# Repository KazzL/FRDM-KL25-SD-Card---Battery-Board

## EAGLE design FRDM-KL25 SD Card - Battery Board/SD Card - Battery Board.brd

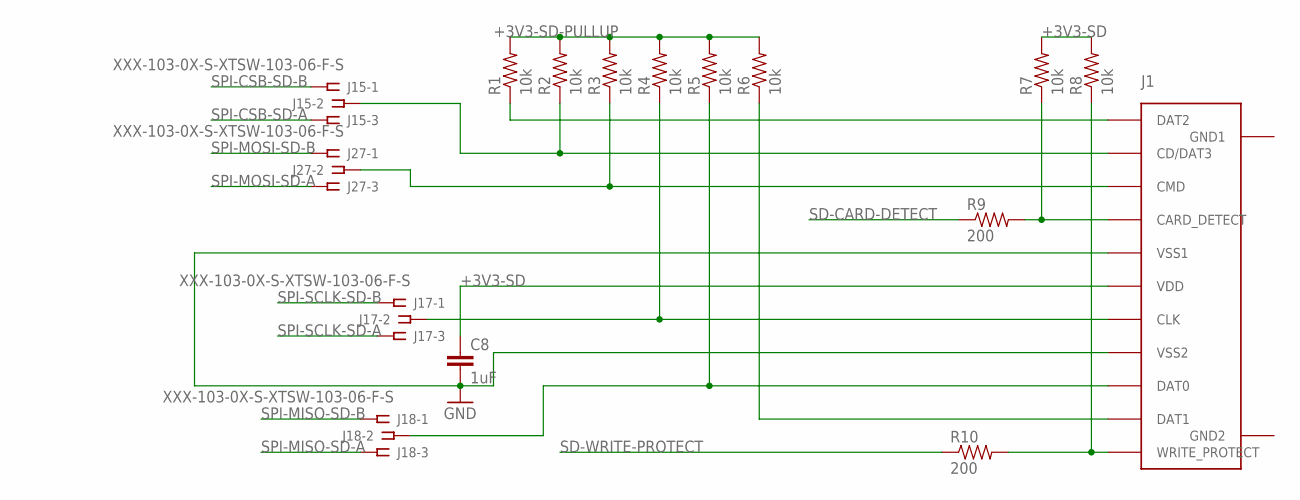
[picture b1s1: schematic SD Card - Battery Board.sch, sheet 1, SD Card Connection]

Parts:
C8: 1uF; C0402
J1: SD_CARD_SLOT; 693061010911
J15, J17, J18, J27: XXX-103-0X-S-XTSW-103-06-F-S; XXX-103-0X-S-X
R1, R2, R3, R4, R5, R6, R7, R8: 10k; R0603
R9, R10: 200; R0603

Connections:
+3V3-SD: C8.1, J1.P$4 (VDD), R7.2, R8.2; also elsewhere on the board
+3V3-SD-PULLUP: R1.2, R2.2, R3.2, R4.2, R5.2, R6.2; also elsewhere on the board
GND: C8.2, J1.P$3 (VSS1), J1.P$6 (VSS2); also elsewhere on the board
unnamed: J1.P$9 (DAT2), R1.1
unnamed: J1.P$10 (CARD_DETECT), R7.1, R9.2
unnamed: J1.P$1 (CD/DAT3), J15.2, R2.1
unnamed: J1.P$8 (DAT1), R6.1
unnamed: J1.P$11 (WRITE_PROTECT), R8.1, R10.2
unnamed: J1.P$2 (CMD), J27.2, R3.1
unnamed: J1.P$5 (CLK), J17.2, R4.1
unnamed: J1.P$7 (DAT0), J18.2, R5.1
SD-CARD-DETECT: R9.1; also elsewhere on the board
SD-WRITE-PROTECT: R10.1; also elsewhere on the board
SPI-CSB-SD-A: J15.3; also elsewhere on the board
SPI-CSB-SD-B: J15.1; also elsewhere on the board
SPI-MISO-SD-A: J18.3; also elsewhere on the board
SPI-MISO-SD-B: J18.1; also elsewhere on the board
SPI-MOSI-SD-A: J27.3; also elsewhere on the board
SPI-MOSI-SD-B: J27.1; also elsewhere on the board
SPI-SCLK-SD-A: J17.3; also elsewhere on the board
SPI-SCLK-SD-B: J17.1; also elsewhere on the board

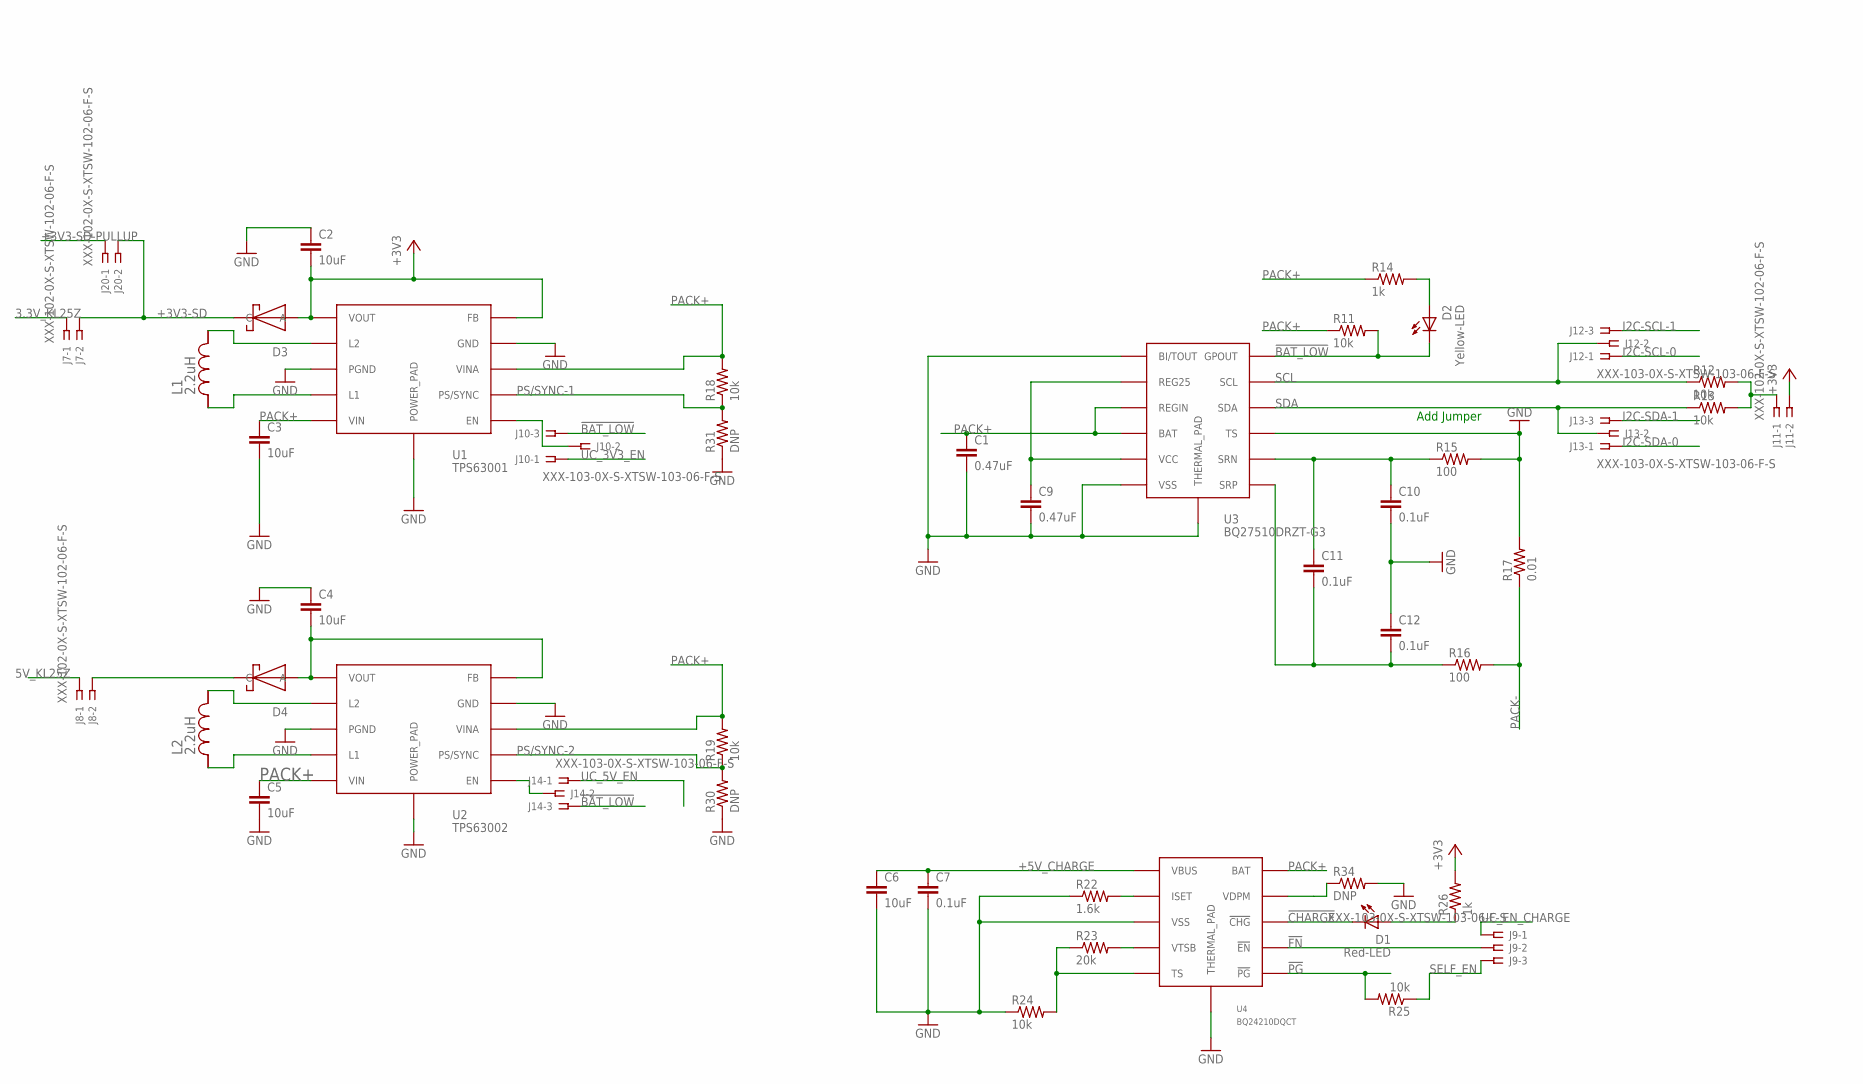
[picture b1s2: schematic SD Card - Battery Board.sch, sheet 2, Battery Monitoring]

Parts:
C1, C9: 0.47uF; C0402
C2, C3, C4, C5, C6: 10uF; C0402
C7, C10, C11, C12: 0.1uF; C0402
D1: Red-LED; 1.25X1.4
D2: Yellow-LED; 1.25X1.4
D3, D4: SCHOTTKY; SC-90
J7, J8, J11, J20: XXX-102-0X-S-XTSW-102-06-F-S; XXX-102-0X-S-X
J9, J10, J12, J13, J14: XXX-103-0X-S-XTSW-103-06-F-S; XXX-103-0X-S-X
L1, L2: 2.2uH; NRS401X
R11, R12, R13, R18, R19, R24, R25: 10k; R0402
R14, R26: 1k; R0402
R15, R16: 100; R0402
R17: 0.01; R0603
R22: 1.6k; R0402
R23: 20k; R0402
R30, R31, R34: DNP; R0402
U1: TPS63001; VFDFN-10
U2: TPS63002; VFDFN-10
U3: BQ27510DRZT-G3; VFDFN-12
U4: BQ24210DQCT; WFDFN-10

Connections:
3.3V_KL25Z: J7.1; also elsewhere on the board
5V_KL25Z: J8.1; also elsewhere on the board
!BAT_LOW: D2.P$2 (C), J10.3, J14.3, R11.2, U3.P$12 (GPOUT)
!CHARGE: D1.P$2 (C), U4.P$8 (!CHG)
!FN: J9.2, U4.P$7 (!EN)
!PG: R25.2, U4.P$6 (!PG)
+3V3: C2.2, D3.P$2 (A), J11.2, R26.2, U1.P$1 (VOUT), U1.P$10 (FB)
+3V3-SD: D3.P$1 (C), J7.2, J20.2; also elsewhere on the board
+3V3-SD-PULLUP: J20.1; also elsewhere on the board
+5V_CHARGE: C6.1, C7.1, U4.P$1 (VBUS); also elsewhere on the board
GND: C1.2, C2.1, C3.2, C4.1, C5.2, C6.2, C7.2, C9.2, C10.2, C12.1, R15.2, R17.2, R22.1, R24.1, R30.1, R31.1, R34.2, U1.P$3 (PGND), U1.P$9 (GND), U1.P$11 (POWER_PAD), U2.P$3 (PGND), U2.P$9 (GND), U2.P$11 (POWER_PAD), U3.P$1 (BI/TOUT), U3.P$6 (VSS), U3.P$9 (TS), U3.P$13 (THERMAL_PAD), U4.P$3 (VSS), U4.P$11 (THERMAL_PAD); also elsewhere on the board
I2C-SCL-0: J12.1; also elsewhere on the board
I2C-SCL-1: J12.3; also elsewhere on the board
I2C-SDA-0: J13.1; also elsewhere on the board
I2C-SDA-1: J13.3; also elsewhere on the board
unnamed: C9.1, U3.P$2 (REG25), U3.P$5 (VCC)
unnamed: J10.2, U1.P$6 (EN)
unnamed: R34.1, U4.P$9 (VDPM)
unnamed: J11.1, R12.2, R13.2
unnamed: D2.P$1 (A), R14.2
unnamed: C11.2, C12.2, R16.1, U3.P$7 (SRP)
unnamed: C10.1, C11.1, R15.1, U3.P$8 (SRN)
unnamed: L1.P$1 (1), U1.P$2 (L2)
unnamed: L1.P$2 (2), U1.P$4 (L1)
unnamed: D1.P$1 (A), R26.1
unnamed: J14.2, U2.P$6 (EN)
unnamed: L2.P$1 (1), U2.P$2 (L2)
unnamed: L2.P$2 (2), U2.P$4 (L1)
unnamed: D4.P$1 (C), J8.2
unnamed: C4.2, D4.P$2 (A), U2.P$1 (VOUT), U2.P$10 (FB)
unnamed: R22.2, U4.P$2 (ISET)
unnamed: R23.2, U4.P$4 (VTSB)
unnamed: R23.1, R24.2, U4.P$5 (TS)
PACK+: C1.1, C3.1, C5.1, R11.1, R14.1, R18.2, R19.2, U1.P$5 (VIN), U1.P$8 (VINA), U2.P$5 (VIN), U2.P$8 (VINA), U3.P$3 (REGIN), U3.P$4 (BAT), U4.P$10 (BAT); also elsewhere on the board
PACK-: R16.2, R17.1; also elsewhere on the board
PS/SYNC-1: R18.1, R31.2, U1.P$7 (PS/SYNC)
PS/SYNC-2: R19.1, R30.2, U2.P$7 (PS/SYNC)
SCL: J12.2, R12.1, U3.P$11 (SCL)
SDA: J13.2, R13.1, U3.P$10 (SDA)
SELF_EN: J9.3, R25.1
UC_3V3_EN: J10.1; also elsewhere on the board
UC_5V_EN: J14.1; also elsewhere on the board
UC_EN_CHARGE: J9.1; also elsewhere on the board

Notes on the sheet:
Add Jumper

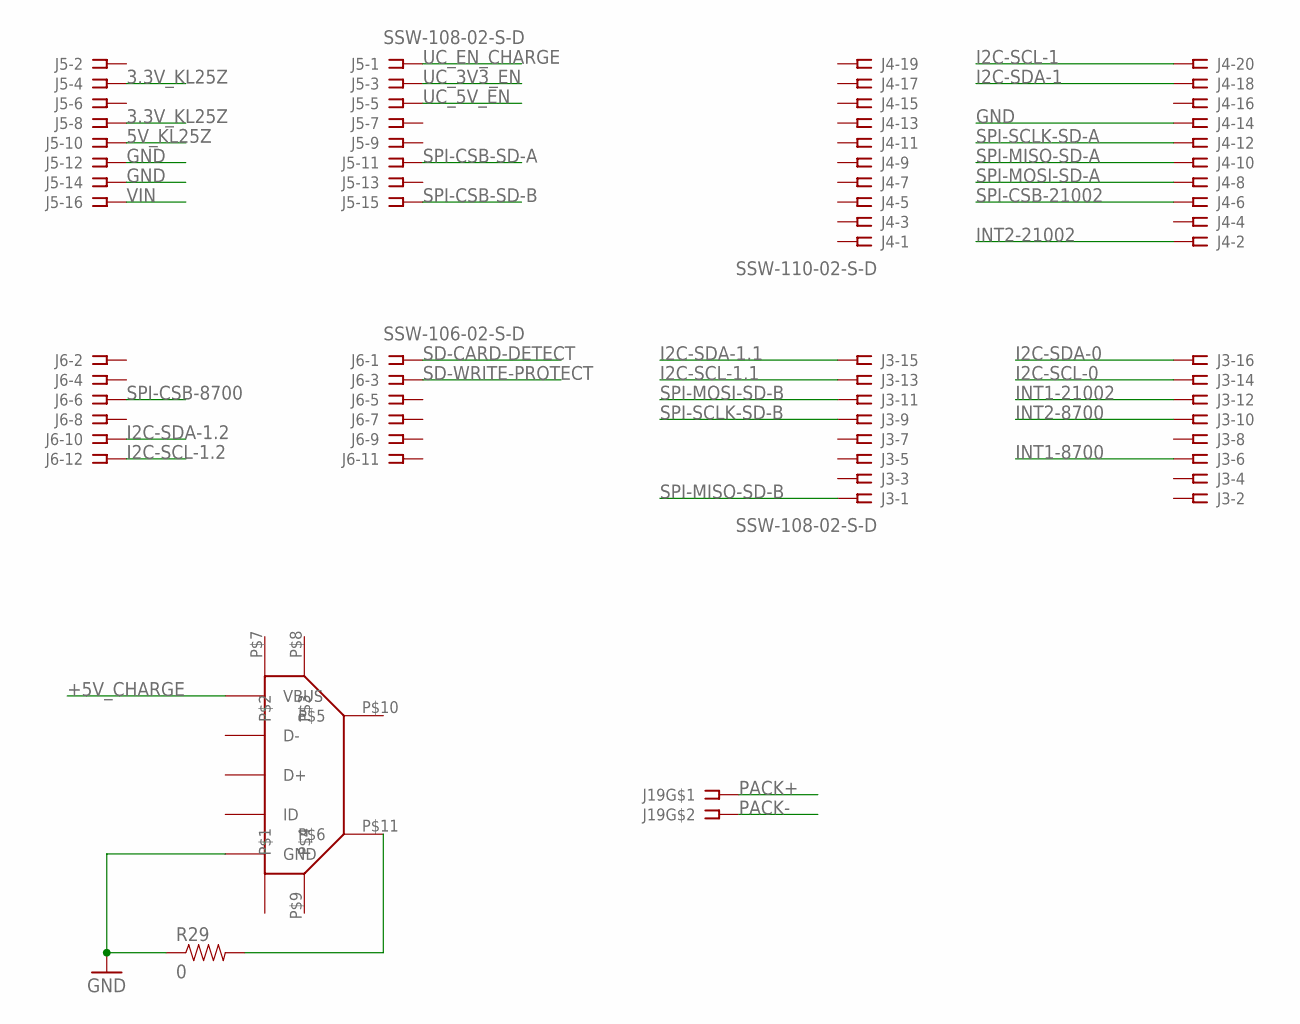
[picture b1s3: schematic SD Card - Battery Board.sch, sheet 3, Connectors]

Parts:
J2: USB-MICROSD-47346-001; SD47346-001-USB-MICRO-MOLEX
J3, J5: SSW-108-02-S-D
J4: SSW-110-02-S-D
J6: SSW-106-02-S-D
J19: 501568-0207-V2; 50156-0207
R29: 0; R0402

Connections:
3.3V_KL25Z: J5.4, J5.8; also elsewhere on the board
5V_KL25Z: J5.10; also elsewhere on the board
+5V_CHARGE: J2.P$1 (VBUS); also elsewhere on the board
GND: J2.P$5 (GND), J4.14, J5.12, J5.14, R29.1; also elsewhere on the board
I2C-SCL-0: J3.14; also elsewhere on the board
I2C-SCL-1: J4.20; also elsewhere on the board
I2C-SCL-1.1: J3.13
I2C-SCL-1.2: J6.12
I2C-SDA-0: J3.16; also elsewhere on the board
I2C-SDA-1: J4.18; also elsewhere on the board
I2C-SDA-1.1: J3.15
I2C-SDA-1.2: J6.10
INT1-8700: J3.6
INT1-21002: J3.12
INT2-8700: J3.10
INT2-21002: J4.2
unnamed: J2.P$11, R29.2
PACK+: J19.P$1; also elsewhere on the board
PACK-: J19.P$2; also elsewhere on the board
SD-CARD-DETECT: J6.1; also elsewhere on the board
SD-WRITE-PROTECT: J6.3; also elsewhere on the board
SPI-CSB-8700: J6.6
SPI-CSB-21002: J4.6
SPI-CSB-SD-A: J5.11; also elsewhere on the board
SPI-CSB-SD-B: J5.15; also elsewhere on the board
SPI-MISO-SD-A: J4.10; also elsewhere on the board
SPI-MISO-SD-B: J3.1; also elsewhere on the board
SPI-MOSI-SD-A: J4.8; also elsewhere on the board
SPI-MOSI-SD-B: J3.11; also elsewhere on the board
SPI-SCLK-SD-A: J4.12; also elsewhere on the board
SPI-SCLK-SD-B: J3.9; also elsewhere on the board
UC_3V3_EN: J5.3; also elsewhere on the board
UC_5V_EN: J5.5; also elsewhere on the board
UC_EN_CHARGE: J5.1; also elsewhere on the board
VIN: J5.16

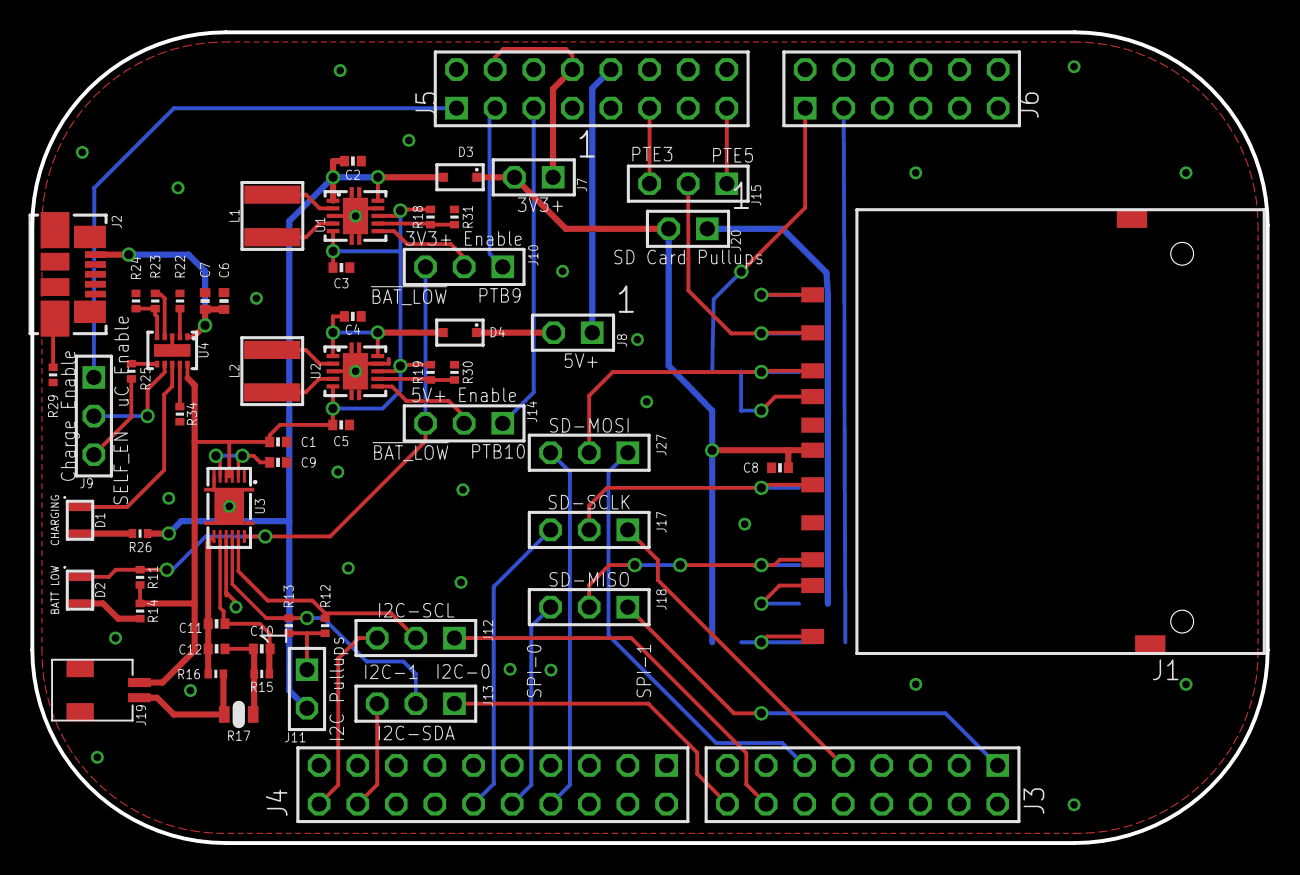
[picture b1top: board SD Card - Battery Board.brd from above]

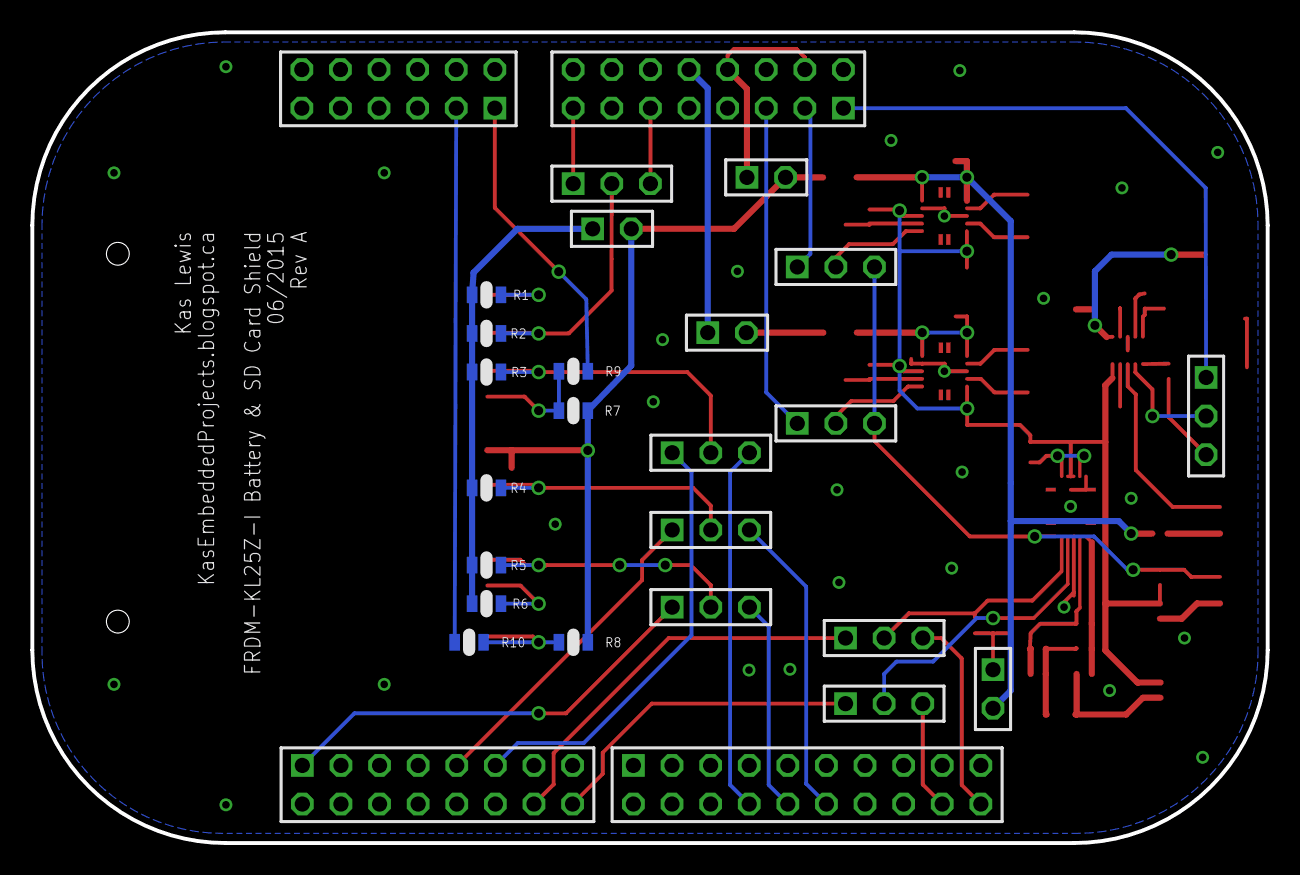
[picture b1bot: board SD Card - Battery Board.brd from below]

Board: 2 copper layers, 81.3 x 53.3 mm, 70 parts (14 on the bottom side), 62 nets.

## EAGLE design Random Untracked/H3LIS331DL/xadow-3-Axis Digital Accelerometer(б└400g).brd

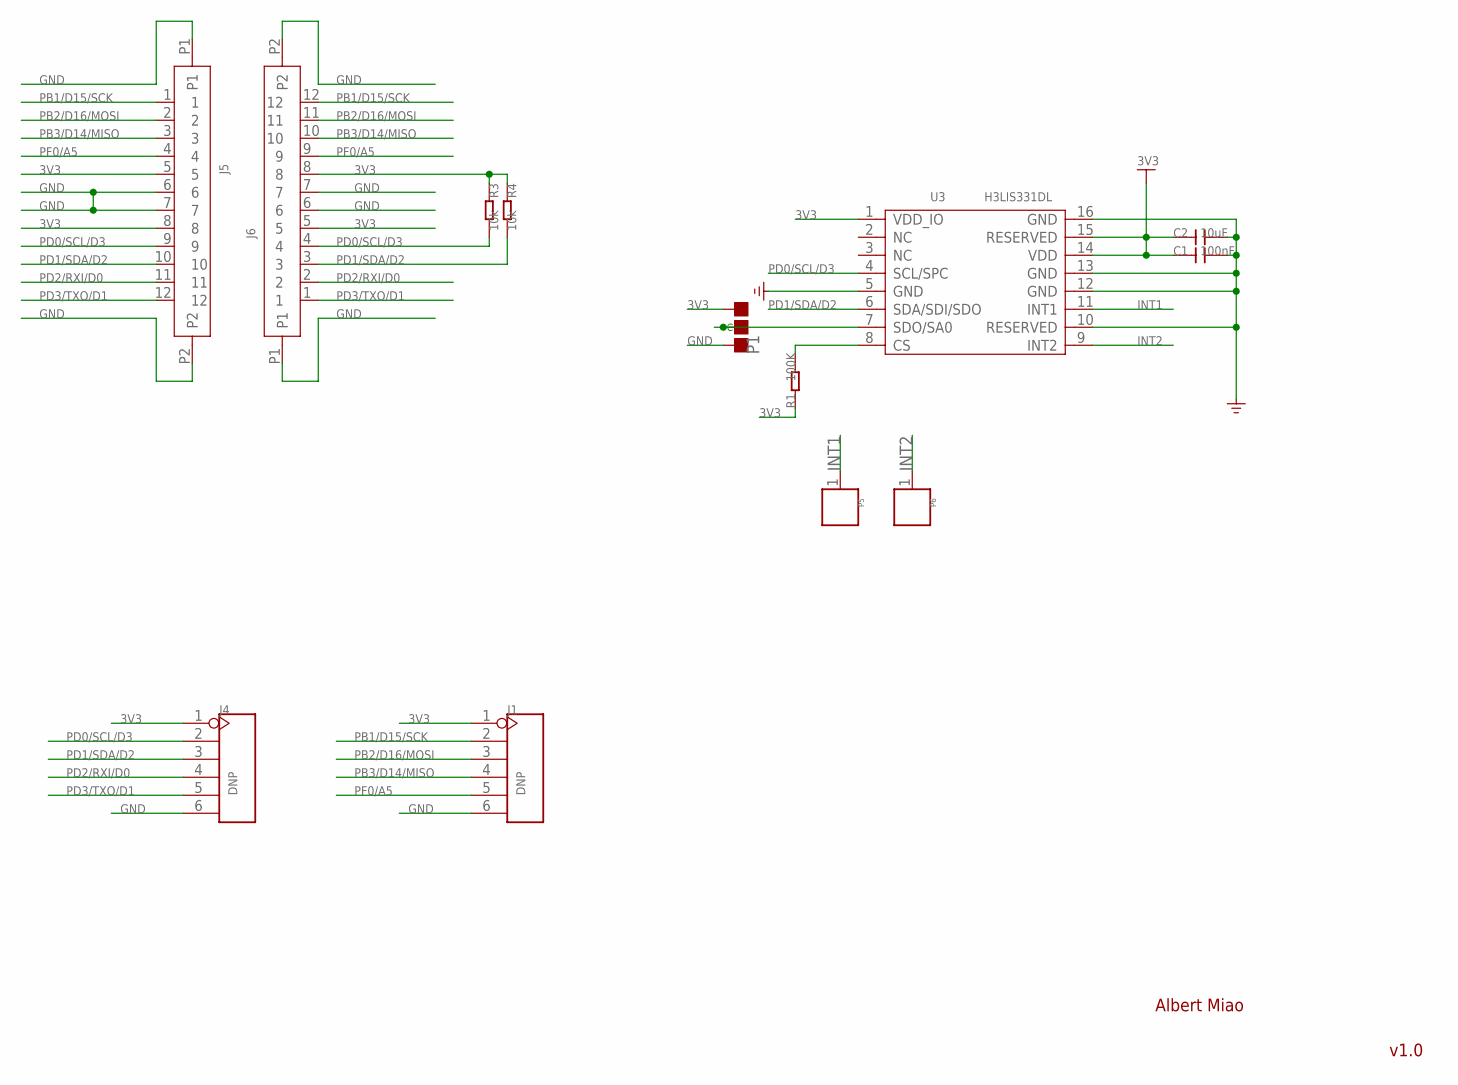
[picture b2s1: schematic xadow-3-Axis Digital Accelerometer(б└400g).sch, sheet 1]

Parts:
C1: 100nF; C0603
C2: 10uF; C0805
J1, J4: DNP; 6P-2.54-65/35MIL
J5, J6: FPC052002-12LT-FH12-12S-0.5SH; 12P-0.5-NEW
P1: PAD-JUMPER-3P-40*40; 3P-SMD-4.1X1.5
P5, P6: PAD'60/30'; 1P-65/35MIL
R1: 100K; R0603
R3, R4: 10k; R0603
U3: H3LIS331DL; TFLGA-16

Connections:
3V3: C1.1, C2.1, J1.1, J4.1, J5.5, J5.8, J6.5, J6.8, P1.00 (L), R1.1, R3.1, R4.1, U3.1 (VDD_IO), U3.14 (VDD), U3.15 (RESERVED)
GND: C1.2, C2.2, J1.6, J4.6, J5.6, J5.7, J5.P1, J5.P2, J6.6, J6.7, J6.P1, J6.P2, P1.11 (R), U3.5 (GND), U3.10 (RESERVED), U3.12 (GND), U3.13 (GND), U3.16 (GND)
INT1: P5.1, U3.11 (INT1)
INT2: P6.1, U3.9 (INT2)
unnamed: R1.2, U3.8 (CS)
unnamed: P1.MM (C), U3.7 (SDO/SA0)
PB1/D15/SCK: J1.2, J5.1, J6.12
PB2/D16/MOSI: J1.3, J5.2, J6.11
PB3/D14/MISO: J1.4, J5.3, J6.10
PD0/SCL/D3: J4.2, J5.9, J6.4, R3.2, U3.4 (SCL/SPC)
PD1/SDA/D2: J4.3, J5.10, J6.3, R4.2, U3.6 (SDA/SDI/SDO)
PD2/RXI/D0: J4.4, J5.11, J6.2
PD3/TXO/D1: J4.5, J5.12, J6.1
PF0/A5: J1.5, J5.4, J6.9

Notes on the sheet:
Albert Miao
v1.0

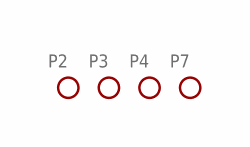
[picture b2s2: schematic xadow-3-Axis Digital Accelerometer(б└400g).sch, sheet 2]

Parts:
P2, P3, P4, P7: PAD-MARK; ROUND-MARK-1.0

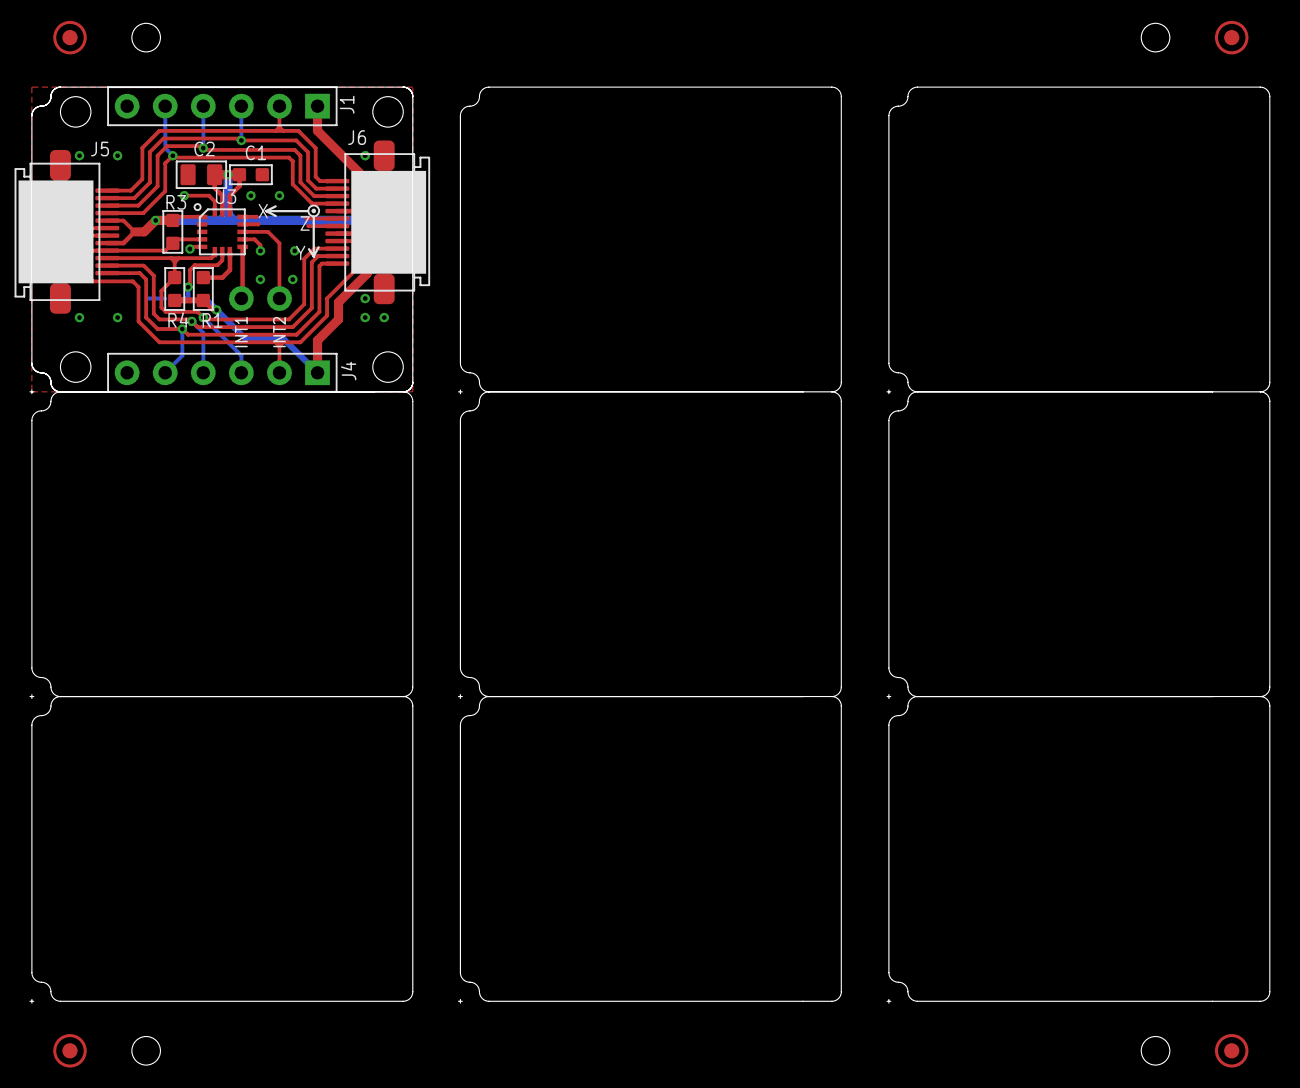
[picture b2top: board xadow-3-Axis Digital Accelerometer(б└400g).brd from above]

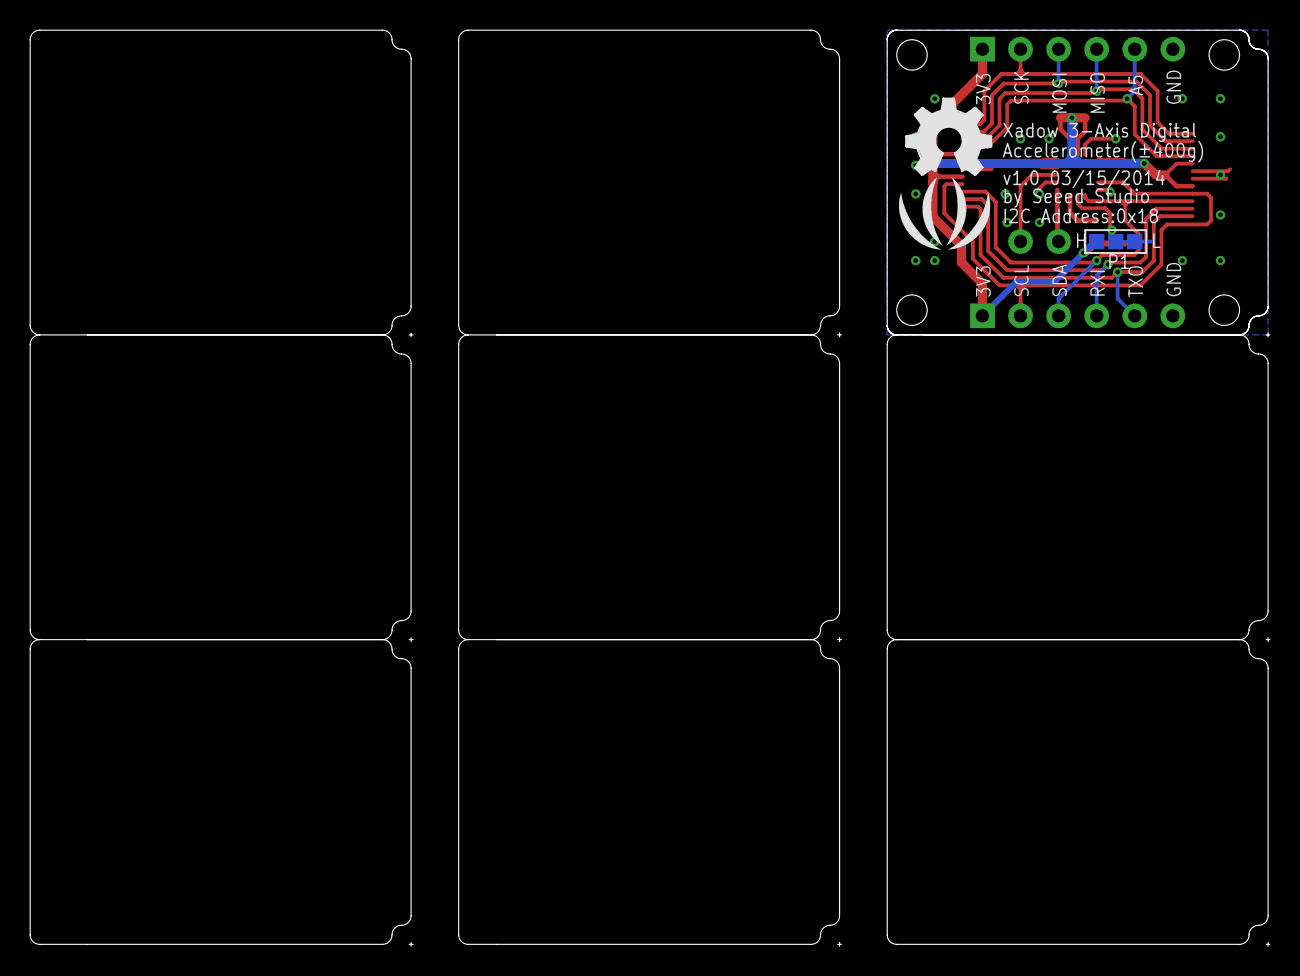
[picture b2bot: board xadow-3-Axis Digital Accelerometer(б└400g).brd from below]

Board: 2 copper layers, 82.7 x 61.1 mm, 19 parts (3 on the bottom side), 14 nets.

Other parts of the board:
U$2: LOGO_SILK
U$3: OSHW_FILLX200_NOTEXT

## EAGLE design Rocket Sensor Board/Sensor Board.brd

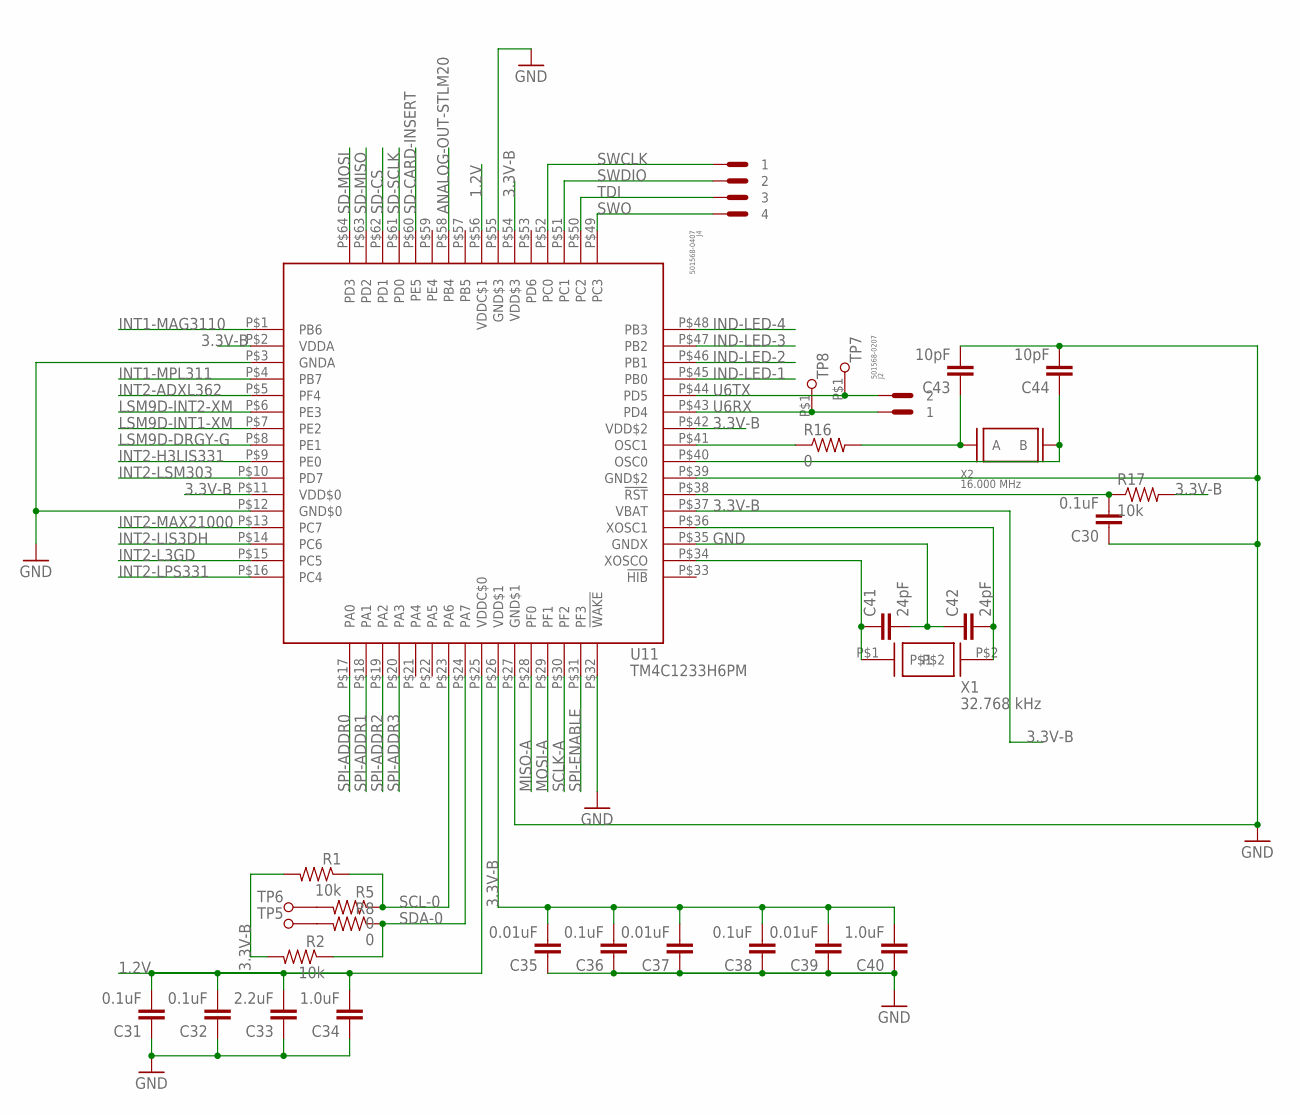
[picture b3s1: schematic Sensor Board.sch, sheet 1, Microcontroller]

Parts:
C30, C31, C32, C36, C38: 0.1uF; C0402
C33: 2.2uF; C0402
C34, C40: 1.0uF; C0402
C35, C37, C39: 0.01uF; C0402
C41, C42: 24pF; C0402
C43, C44: 10pF; C0402
J2: 501568-0207
J4: 501568-0407
R1, R2, R17: 10k; R0402
R5, R8, R16: 0; R0402
TP5, TP6, TP7, TP8: TESTPAD(ROUND)
U11: TM4C1233H6PM; S-PQFP-G64
X1: 32.768 kHz; 2-SMD(3.2X1.5)
X2: 16.000 MHz; 4-SMD(3.2X2.5)

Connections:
1.2V: C31.2, C32.2, C33.2, C34.2, U11.P$25 (VDDC$0), U11.P$56 (VDDC$1)
3.3V-B: C35.2, C36.2, C37.2, C38.2, C39.2, C40.2, R1.2, R2.2, R17.2, U11.P$2 (VDDA), U11.P$11 (VDD$0), U11.P$26 (VDD$1), U11.P$37 (VBAT), U11.P$42 (VDD$2), U11.P$54 (VDD$3); also elsewhere on the board
ANALOG-OUT-STLM20: U11.P$58 (PB4); also elsewhere on the board
GND: C30.1, C31.1, C32.1, C33.1, C34.1, C35.1, C36.1, C37.1, C38.1, C39.1, C40.1, C41.2, C42.1, C43.2, C44.2, U11.P$3 (GNDA), U11.P$12 (GND$0), U11.P$27 (GND$1), U11.P$32 (!WAKE), U11.P$35 (GNDX), U11.P$39 (GND$2), U11.P$55 (GND$3); also elsewhere on the board
IND-LED-1: U11.P$45 (PB0); also elsewhere on the board
IND-LED-2: U11.P$46 (PB1); also elsewhere on the board
IND-LED-3: U11.P$47 (PB2); also elsewhere on the board
IND-LED-4: U11.P$48 (PB3); also elsewhere on the board
INT1-MAG3110: U11.P$1 (PB6); also elsewhere on the board
INT1-MPL311: U11.P$4 (PB7); also elsewhere on the board
INT2-ADXL362: U11.P$5 (PF4); also elsewhere on the board
INT2-H3LIS331: U11.P$9 (PE0); also elsewhere on the board
INT2-L3GD: U11.P$15 (PC5); also elsewhere on the board
INT2-LIS3DH: U11.P$14 (PC6); also elsewhere on the board
INT2-LPS331: U11.P$16 (PC4); also elsewhere on the board
INT2-LSM303: U11.P$10 (PD7); also elsewhere on the board
INT2-MAX21000: U11.P$13 (PC7); also elsewhere on the board
LSM9D-DRGY-G: U11.P$8 (PE1); also elsewhere on the board
LSM9D-INT1-XM: U11.P$7 (PE2); also elsewhere on the board
LSM9D-INT2-XM: U11.P$6 (PE3); also elsewhere on the board
MISO-A: U11.P$28 (PF0); also elsewhere on the board
MOSI-A: U11.P$29 (PF1); also elsewhere on the board
unnamed: C30.2, R17.1, U11.P$38 (!RST)
unnamed: C42.2, U11.P$36 (XOSC1), X1.P$2
unnamed: C41.1, U11.P$34 (XOSCO), X1.P$1
unnamed: C43.1, R16.2, X2.P$1 (A)
unnamed: C44.1, U11.P$40 (OSC0), X2.P$3 (B)
unnamed: R16.1, U11.P$41 (OSC1)
unnamed: R5.2, TP6.P$1
unnamed: R8.2, TP5.P$1
SCL-0: R1.1, R5.1, U11.P$23 (PA6); also elsewhere on the board
SCLK-A: U11.P$30 (PF2); also elsewhere on the board
SD-CARD-INSERT: U11.P$60 (PE5); also elsewhere on the board
SD-CS: U11.P$62 (PD1); also elsewhere on the board
SD-MISO: U11.P$63 (PD2); also elsewhere on the board
SD-MOSI: U11.P$64 (PD3); also elsewhere on the board
SD-SCLK: U11.P$61 (PD0); also elsewhere on the board
SDA-0: R2.1, R8.1, U11.P$24 (PA7); also elsewhere on the board
SPI-ADDR0: U11.P$17 (PA0); also elsewhere on the board
SPI-ADDR1: U11.P$18 (PA1); also elsewhere on the board
SPI-ADDR2: U11.P$19 (PA2); also elsewhere on the board
SPI-ADDR3: U11.P$20 (PA3); also elsewhere on the board
SPI-ENABLE: U11.P$31 (PF3)
SWCLK: J4.P$1 (1), U11.P$52 (PC0)
SWDIO: J4.P$2 (2), U11.P$51 (PC1)
SWO: J4.P$4 (4), U11.P$49 (PC3)
TDI: J4.P$3 (3), U11.P$50 (PC2)
U6RX: J2.P$1 (1), TP8.P$1, U11.P$43 (PD4)
U6TX: J2.P$2 (2), TP7.P$1, U11.P$44 (PD5)

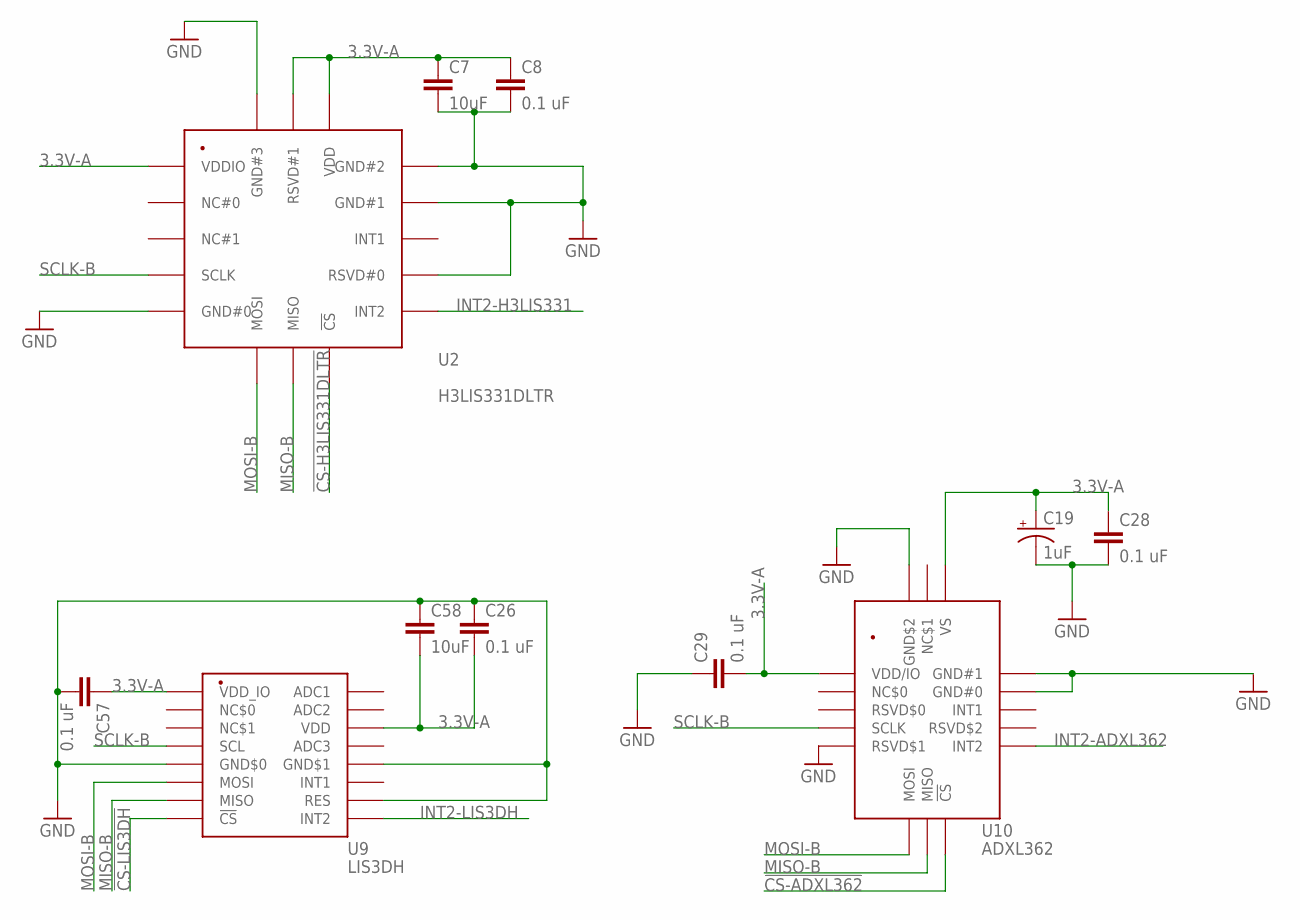
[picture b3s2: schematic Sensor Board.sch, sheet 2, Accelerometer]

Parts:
C7, C58: 10uF; C0603
C8, C26, C28, C29, C57: 0.1 uF; C0402
C19: 1uF; EIA6032
U2: H3LIS331DLTR; LGA-16(3X3)
U9: LIS3DH; LGA-16(3X3)
U10: ADXL362; LGA-16(3X3.25)

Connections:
3.3V-A: C7.1, C8.1, C19.P$1 (+), C26.2, C28.1, C29.2, C57.1, C58.2, U2.P$1 (VDDIO), U2.P$14 (VDD), U2.P$15 (RSVD#1), U9.P$1 (VDD_IO), U9.P$14 (VDD), U10.P$1 (VDD/IO), U10.P$14 (VS); also elsewhere on the board
!CS-ADXL362: U10.P$8 (!CS); also elsewhere on the board
!CS-H3LIS331DLTR: U2.P$8 (!CS); also elsewhere on the board
!CS-LIS3DH: U9.P$8 (!CS); also elsewhere on the board
GND: C7.2, C8.2, C19.P$2 (-), C26.1, C28.2, C29.1, C57.2, C58.1, U2.P$5 (GND#0), U2.P$10 (RSVD#0), U2.P$12 (GND#1), U2.P$13 (GND#2), U2.P$16 (GND#3), U9.P$5 (GND$0), U9.P$10 (RES), U9.P$12 (GND$1), U10.P$5 (RSVD$1), U10.P$12 (GND#0), U10.P$13 (GND#1), U10.P$16 (GND$2); also elsewhere on the board
INT2-ADXL362: U10.P$9 (INT2); also elsewhere on the board
INT2-H3LIS331: U2.P$9 (INT2); also elsewhere on the board
INT2-LIS3DH: U9.P$9 (INT2); also elsewhere on the board
MISO-B: U2.P$7 (MISO), U9.P$7 (MISO), U10.P$7 (MISO); also elsewhere on the board
MOSI-B: U2.P$6 (MOSI), U9.P$6 (MOSI), U10.P$6 (MOSI); also elsewhere on the board
SCLK-B: U2.P$4 (SCLK), U9.P$4 (SCL), U10.P$4 (SCLK); also elsewhere on the board

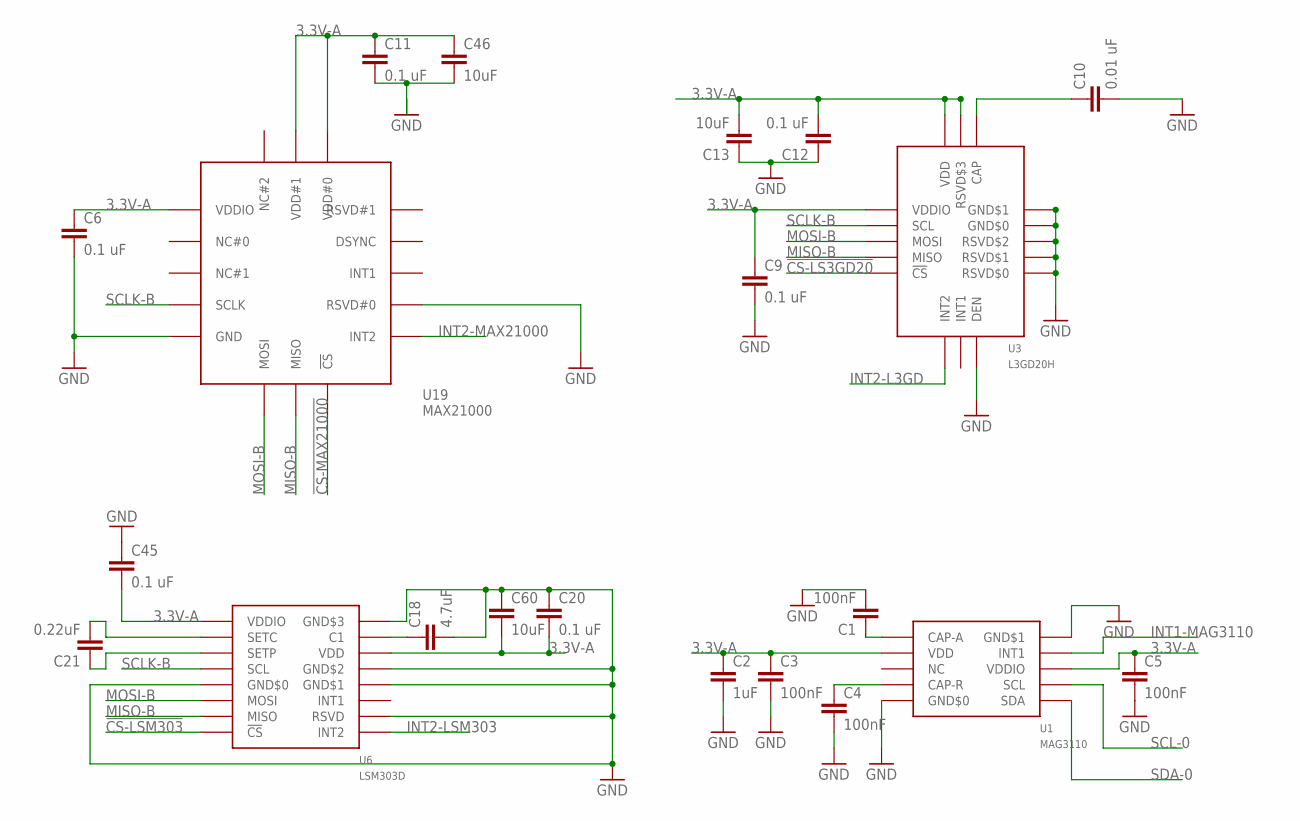
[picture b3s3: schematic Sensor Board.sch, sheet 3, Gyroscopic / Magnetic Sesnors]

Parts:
C1, C3, C4, C5: 100nF; C0402
C2: 1uF; C0402
C6, C9, C11, C12, C20, C45: 0.1 uF; C0402
C10: 0.01 uF; C0402
C13, C46, C60: 10uF; C0603
C18: 4.7uF; C0603
C21: 0.22uF; C0603
U1: MAG3110; DFN-10(2X2)
U3: L3GD20H; LGA-16(3X3)
U6: LSM303D; LGA-16(3X3)
U19: MAX21000; LGA-16(3X3)

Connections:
3.3V-A: C2.1, C3.1, C5.1, C6.1, C9.1, C11.1, C12.2, C13.2, C20.2, C45.2, C46.1, C60.2, U1.P$2 (VDD), U1.P$8 (VDDIO), U3.P$1 (VDDIO), U3.P$15 (RSVD$3), U3.P$16 (VDD), U6.P$1 (VDDIO), U6.P$14 (VDD), U19.P$1 (VDDIO), U19.P$14 (VDD#0), U19.P$15 (VDD#1); also elsewhere on the board
!CS-LS3GD20: U3.P$5 (!CS); also elsewhere on the board
!CS-LSM303: U6.P$8 (!CS); also elsewhere on the board
!CS-MAX21000: U19.P$8 (!CS); also elsewhere on the board
GND: C1.2, C2.2, C3.2, C4.2, C5.2, C6.2, C9.2, C10.2, C11.2, C12.1, C13.1, C18.2, C20.1, C45.1, C46.2, C60.1, U1.P$5 (GND$0), U1.P$10 (GND$1), U3.P$8 (DEN), U3.P$9 (RSVD$0), U3.P$10 (RSVD$1), U3.P$11 (RSVD$2), U3.P$12 (GND$0), U3.P$13 (GND$1), U6.P$5 (GND$0), U6.P$10 (RSVD), U6.P$12 (GND$1), U6.P$13 (GND$2), U6.P$16 (GND$3), U19.P$5 (GND), U19.P$10 (RSVD#0); also elsewhere on the board
INT1-MAG3110: U1.P$9 (INT1); also elsewhere on the board
INT2-L3GD: U3.P$6 (INT2); also elsewhere on the board
INT2-LSM303: U6.P$9 (INT2); also elsewhere on the board
INT2-MAX21000: U19.P$9 (INT2); also elsewhere on the board
MISO-B: U3.P$4 (MISO), U6.P$7 (MISO), U19.P$7 (MISO); also elsewhere on the board
MOSI-B: U3.P$3 (MOSI), U6.P$6 (MOSI), U19.P$6 (MOSI); also elsewhere on the board
unnamed: C1.1, U1.P$1 (CAP-A)
unnamed: C4.1, U1.P$4 (CAP-R)
unnamed: C10.1, U3.P$14 (CAP)
unnamed: C18.1, U6.P$15 (C1)
unnamed: C21.2, U6.P$2 (SETC)
unnamed: C21.1, U6.P$3 (SETP)
SCL-0: U1.P$7 (SCL); also elsewhere on the board
SCLK-B: U3.P$2 (SCL), U6.P$4 (SCL), U19.P$4 (SCLK); also elsewhere on the board
SDA-0: U1.P$6 (SDA); also elsewhere on the board

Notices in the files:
parts and their libraries:
SparkFun-Passives: Licensing: CC v3.0 Share-Alike You are welcome to use this library for commercial purposes.
